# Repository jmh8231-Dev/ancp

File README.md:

# ANCP Rocket Motor Test Station (Rev 2.0)

> 고정추진제 로켓 모터(ANCP) 지상시험을 위한 **정밀 계측·점화 제어 스테이션**  
> 고정밀 아날로그 체인(로드셀/압력/열전대), **안전 중심 점화 시퀀스**, **2″ LCD(LVGL9 + SPI DMA)** GUI, PC 텔레메트리 지원

---

##  주요 기능

- **안전 중심 점화 플로우**
  - 물리 **IGN 스위치** 감지 → 카운트다운 → 온도/추력 인터록 → 핫와이어 제어
  - 모터/보드/PC 준비 상태 점검(미준비 시 시험 중지)
- **정밀 계측 체인**
  - 로드셀(추력), 챔버 압력, 노즐/내부 온도(열전대), IMU 진동
  - 메인/IGN 배터리 **셀 별 전압** + 메인 배터리 전류(INA219)
- **2″ LCD GUI (LVGL v9)**
  - **SPI DMA** 플러시(논블로킹), SquareLine Studio 기반 화면
  - Idle/Test/Config/Cal 페이지, FPS 확보 위해 라인 버퍼 + DMA 이중버퍼
- **EEPROM 기반 설정/보정**
  - **32B 페이지** 체크섬 저장 포맷(캘리브레이션 오프셋/설정값 무결성 보장)
- **PC/RF 텔레메트리**
  - 헤더·길이·페이로드·체크섬으로 구성된 패킷 전송
- **RTOS 태스킹**
  - sensing / gui / comms / control / logging 분리

---

##  하드웨어 개요

| 항목 | 부품 |
|---|---|
| MCU | **STM32H723VGT6** (H7, 12 MHz TCXO) |
| 정밀 ADC | **ADS1262IPW** (ΔΣ, 24-bit) |
| SPI 절연 | **ADuM4151** (MCU–ADC) |
| 기준전압 | **ADR4525D** |
| Op-Amp | **OPA189**, **MCP6022**, **TLV9351** |
| 전류 센서 | **INA219** (메인 배터리) |
| IMU | **BNO085** (I²C) |
| 온도 센서 | **AS6221** (MOSFET 온도) |
| EEPROM | **AT24C08C** (I²C) |
| 전원 | LM2596S-3.3, **CC6-1212DR-E**(±12 V) → **LT3045**(+5 V) / **LT3094**(−5 V) / **TPS79225**(+2.5 V) / **TPS72325**(−2.5 V) |
| 점화 경로 | **TC427** 게이트 드라이버 + **IRF1404** 파워 MOSFET, 물리 **IGN SW** |
| I/O | 2″ LCD, F1–F4 버튼, 부저, USB-UART(FT232RL), RF 모듈, ST-Link, 밸런스 잭 |

**3D 렌더 (Top)**  

**PCB 레이아웃(Top Routed)**  

---

##  펌웨어 개요

- **프레임워크**: STM32Cube HAL (+ FreeRTOS 선택)
- **GUI**: **LVGL v9** / **SquareLine Studio**(UI 설계)
- **LCD 드라이버**: **ST7789 (SPI4 + DMA)**  
  - `fw/Drivers/lcd/LCD_2inch_st7789_v9_dma.c` — ST7789 초기화 + DMA 라인 스트리머  
  - `fw/Drivers/lcd/LVGL9_ST7789_Port_ULP.c` — LVGL9 디스플레이 포트(플러시/세마포어)  
  - `fw/Drivers/board/DEV_Config_h7.c` — SPI4 DMA, D-Cache clean, TIM3 PWM 백라이트, OS-aware delay
- **정밀 ADC(ADS1262)**: SPI(절연) 드라이버, 채널/게인/SPS 매트릭스, 오프셋 CAL
- **EEPROM(AT24C08C)**: 페이지 쓰기/검증, 설정·보정값 저장
- **주요 태스크(권장)**: `task_gui`, `task_sense_fast`, `task_comms`, `task_control`, `task_logging`

### LVGL & LCD 초기화 예시
```c
// main.c
extern void lv_port_disp_init_st7789_v9_ulp(void);

void app_gui_init(void) {
    lv_init();
    lv_port_disp_init_st7789_v9_ulp();  // DMA flush, flush_wait 포함
    // SquareLine 생성 코드 호출 ...
}
```

> **D-Cache ON** 환경에서는 DMA 전 송신 버퍼에 대해 **SCB_CleanDCache_by_Addr()** 처리 필수. 위 파일들에 구현 포함.

---

##  캘리브레이션 & EEPROM 포맷

**ADC Zero-Offset CAL**: *(ch, gain, sps)* 조합별로 오프셋 저장. 부팅 시 전 페이지 스캔 → **이중 체크섬** 검증 → RAM LUT 로드.

```
[32B Page Format]  (1 페이지 = 4개의 Offset)
0-1   : "EP" (헤더)
2     : CH/Gain 상위 3비트(6..3)
3     : SPS
4-7   : OFFSET[ch][gain][sps] (int32/Q-format)
8-13  : 다음 CH/Gain/SPS + OFFSET
14-15 : CHECKSUM #1 (0..13)

16-17 : "EP"
18-19 : CH/Gain/SPS
20-25 : OFFSET
26-29 : 다음 CH/Gain/SPS + OFFSET
30-31 : CHECKSUM #2 (16..29)
```

- **쓰기 시퀀스**: 새 페이지 작성 → 읽기 검증 → 성공 시 구버전 페이지 폐기(저널링)
- **유효성 실패 시**: 기본 오프셋(0)로 부팅 + Cal 페이지 경고 표시

---

## 시험/점화 플로우

1. **Self-check**: 센서 연결/EEPROM 무결성/배터리 상태/PC 준비 여부
2. **IGN SW ON** → **ANCP Test** 모드 자동 진입
3. 로드셀 **Auto-tare** → **카운트다운**(가변)
4. 점화 로직(예시):
```c
if (mosfet_temp < T_th && thrust < F_th)  hotwire_on();
else if (mosfet_temp > T_th && thrust < F_th) { hotwire_off(); show_overheat(); }
else hotwire_off(); // ignition success
```
5. 실시간 데이터 **PC 전송** + 로깅

**전송 패킷(예시)**: `0x48 0x53 | type | len | payload | CRC16`

---

## 스키매틱 스냅샷

**Main Power**  

**MCU**  

**Analog/ADC/Isolation**  

---

## 빌드 & 플래시

- **툴체인**: STM32CubeIDE(H7), ARM GCC, (선택) FreeRTOS  
- **Cube 설정 핵심**  
  - SPI4 TX DMA(FIFO 사용), CS/DC/RST/BL GPIO  
  - TIM3 PWM → 백라이트  
  - 1 ms 타이머 → `lv_tick_inc()`  
  - D-Cache 사용 시 DMA 버퍼 **clean** 처리  
- **빌드**
  ```bash
  git clone https://github.com/jmh8231-Dev/ancp
  # STM32CubeIDE에서 .ioc 열기 → 빌드 → ST-Link로 플래시
  ```
- **첫 부팅**: Idle 화면 → 센서/배터리 상태 확인

---

## 문서 구조

```
ancp/
├─ fw/
│  ├─ Core/                 # CubeMX 생성 코드
│  ├─ Drivers/
│  │  ├─ lvgl/              # LVGL v9
│  │  ├─ lcd/               # LCD_2inch_st7789_v9_dma.c, LVGL9_ST7789_Port_ULP.c
│  │  └─ board/             # DEV_Config_h7.c 등
│  ├─ app/                  # tasks, ads1262, eeprom, telemetry, state machine
│  └─ middleware/           # FreeRTOS(선택)
├─ hw/                      # 회로/PCB/거버
├─ docs/
│  └─ images/               # 사진/스크린샷
└─ README.md
```

## 주의

- 방폭/방염 환경, 방호벽, 소화 장비, **E-Stop** 필수
- 시험 전 인터록/센서/전원/배선 재점검

---

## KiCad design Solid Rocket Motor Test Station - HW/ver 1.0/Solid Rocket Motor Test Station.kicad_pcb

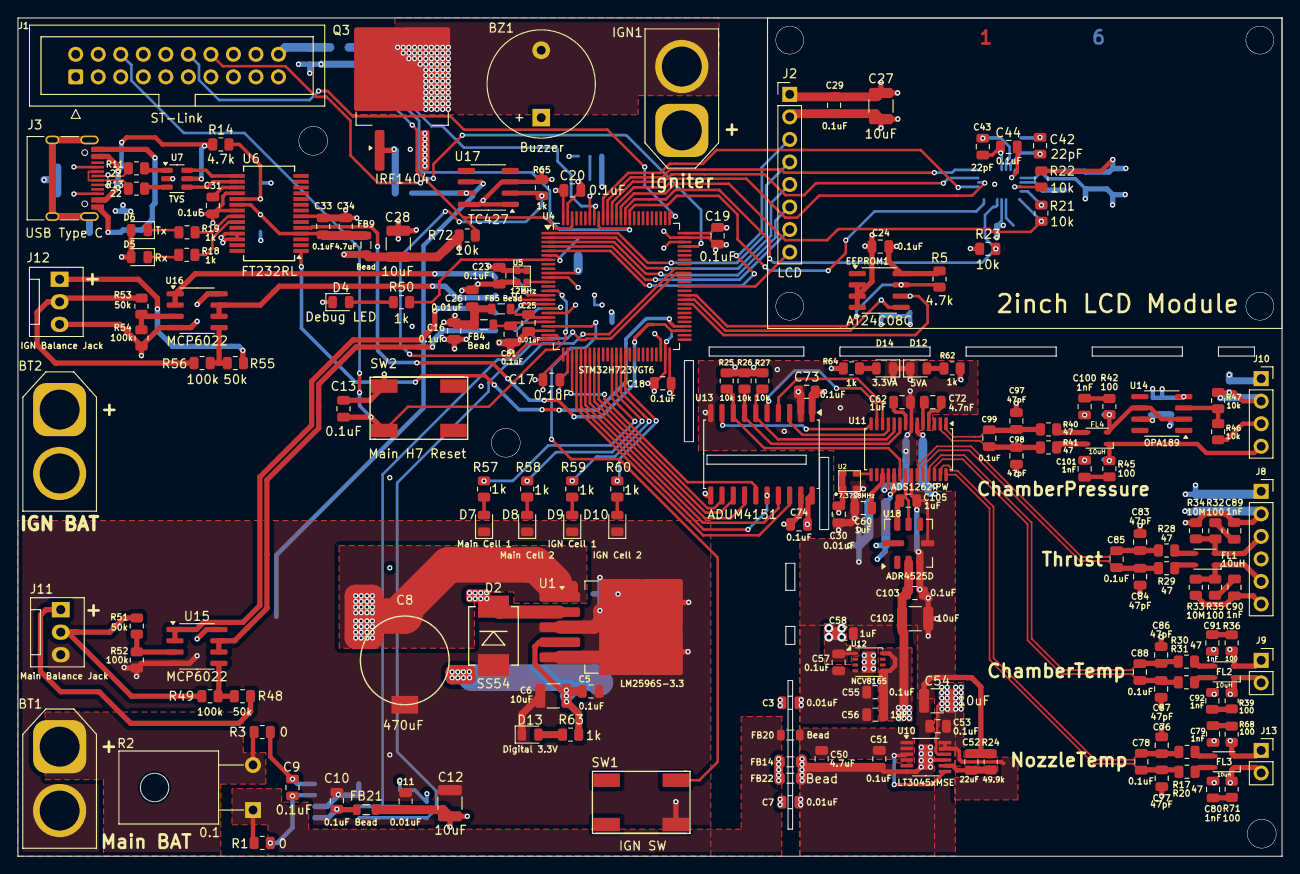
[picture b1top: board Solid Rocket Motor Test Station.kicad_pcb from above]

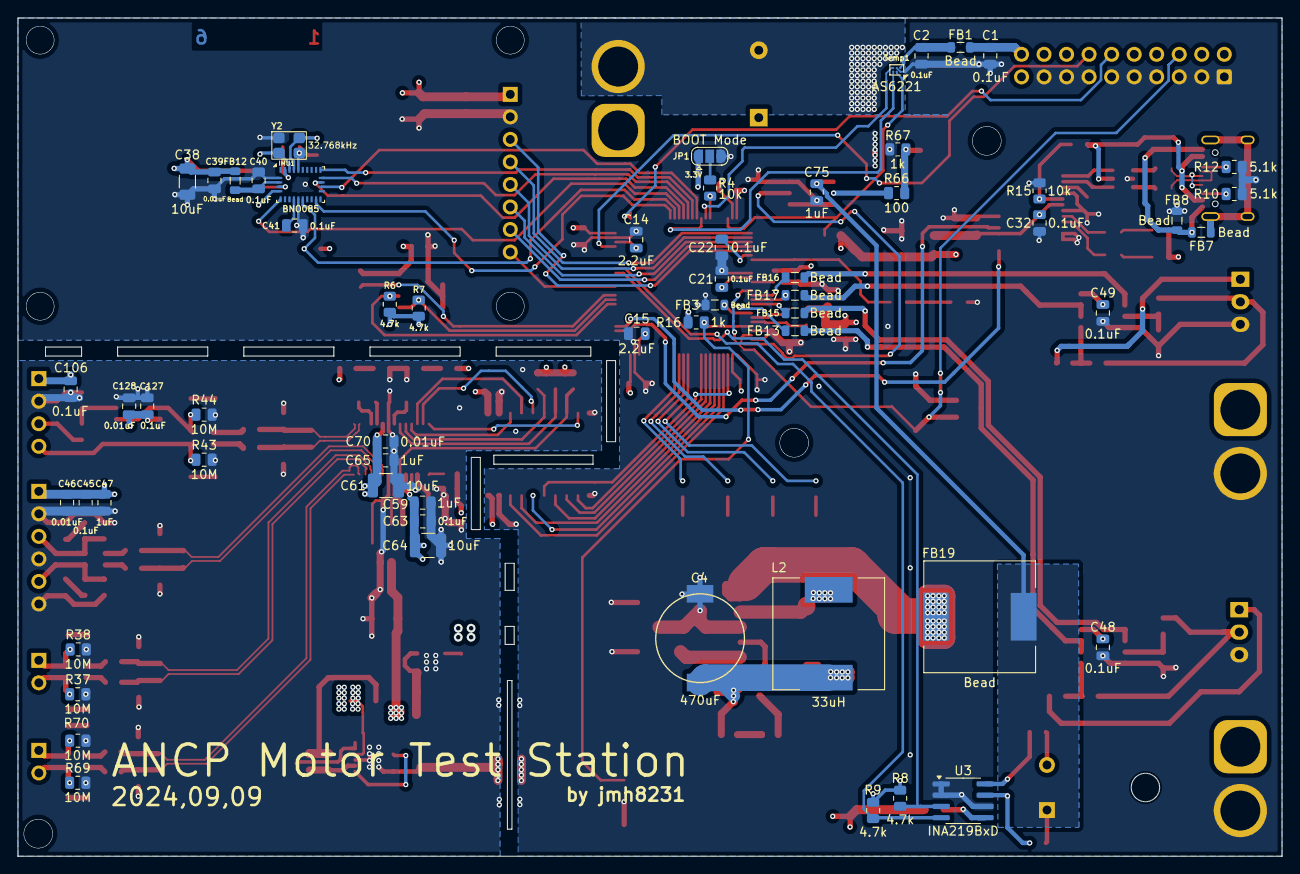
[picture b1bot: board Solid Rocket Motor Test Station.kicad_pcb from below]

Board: 6 copper layers, 142.5 x 94.5 mm, 235 parts (60 on the bottom side), 161 nets.

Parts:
BT1: Main BAT; AMASS_XT60-F_1x02_P7.20mm_Vertical
BT2: IGN BAT; AMASS_XT60-F_1x02_P7.20mm_Vertical
BZ1: Buzzer; Buzzer_12x9.5RM7.6
C1, C2, C5, C9, C10, C13, C16, C17, C18, C19, C20, C21, C22, C23, C24, C29, C31, C32, C33, C40, C41, C44, C45, C48, C49, C51, C53, C55, C57, C63, C73, C74, C78, C81, C85, C88, C99, C103, C106, C127: 0.1uF; C_0805_2012Metric
C3, C7, C11, C25, C26, C30, C39, C46, C70, C128: 0.01uF; C_0805_2012Metric
C4, C8: 470uF; MVG25WV470M
C6, C12, C27, C28, C54, C61, C64, C102: 10uF; C_1210_3225Metric
C14, C15: 2.2uF; C_0805_2012Metric
C34, C50: 4.7uF; C_0805_2012Metric
C38: 10uF; C_1206_3216Metric
C42, C43: 22pF; C_0805_2012Metric
C47, C56, C58, C59, C60, C62, C65, C75, C105: 1uF; C_0805_2012Metric
C52: 22uF; C_0805_2012Metric
C72: 4.7nF; C_0805_2012Metric
C76, C77, C83, C84, C86, C87, C97, C98: 47pF; C_0805_2012Metric
C79, C80, C89, C90, C91, C92, C100, C101: 1nF; C_0805_2012Metric
D2: SS54
D4: Debug LED; LED_0805_2012Metric
D5: Rx; LED_0805_2012Metric
D6: Tx; LED_0805_2012Metric
D7: Main Cell 1; LED_0805_2012Metric
D8: Main Cell 2; LED_0805_2012Metric
D9: IGN Cell 1; LED_0805_2012Metric
D10: IGN Cell 2; LED_0805_2012Metric
D12: 5VA; LED_0805_2012Metric
D13: Digital 3.3V; LED_0805_2012Metric
D14: 3.3VA; LED_0805_2012Metric
EEPROM1: AT24C08C; SOIC-8_3.9x4.9mm_P1.27mm
FB1, FB3, FB4, FB5, FB7, FB8, FB9, FB12, FB13, FB14, FB15, FB16, FB17, FB20, FB21, FB22: Bead; L_0805_2012Metric
FB19: Bead; L_12x12mm_H8mm
FL1, FL2, FL3, FL4: 10uH; L_CommonModeChoke_TDK_ACM2520-2P
IGN1: Igniter; AMASS_XT60-M_1x02_P7.20mm_Vertical
IMU1: BNO085; LGA-28_5.2x3.8mm_P0.5mm
J1: ST-Link; IDC-Header_2x10_P2.54mm_Vertical
J2: LCD; PinHeader_1x08_P2.54mm_Vertical
J3: USB Type C; USB_C_Receptacle_HRO_TYPE-C-31-M-12
J8: Thrust; PinSocket_1x06_P2.54mm_Vertical
J9: ChamberTemp; PinSocket_1x02_P2.54mm_Vertical
J10: ChamberPressure; PinSocket_1x04_P2.54mm_Vertical
J11: Main Balance Jack; FanPinHeader_1x03_P2.54mm_Vertical
J12: IGN Balance Jack; FanPinHeader_1x03_P2.54mm_Vertical
J13: NozzleTemp; PinSocket_1x02_P2.54mm_Vertical
JP1: BOOT Mode; SolderJumper-3_P1.3mm_Open_RoundedPad1.0x1.5mm
L2: 33uH; L_12x12mm_H8mm
Q3: IRF1404; TO-263-2
R1, R3: 0; R_0805_2012Metric
R2: 0.1; TO-126-2_Horizontal_TabDown
R4, R15, R21, R22, R23, R25, R26, R27, R46, R47, R72: 10k; R_0805_2012Metric
R5, R6, R7, R8, R9, R14: 4.7k; R_0805_2012Metric
R10, R12: 5.1k; R_0805_2012Metric
R11, R13: 22; R_0805_2012Metric
R16, R18, R19, R50, R57, R58, R59, R60, R62, R63, R64, R65, R67: 1k; R_0805_2012Metric
R17, R20, R28, R29, R30, R31, R40, R41: 47; R_0805_2012Metric
R24: 49.9k; R_0805_2012Metric
R32, R35, R36, R39, R42, R45, R66, R68, R71: 100; R_0805_2012Metric
R33, R34, R37, R38, R43, R44, R69, R70: 10M; R_0805_2012Metric
R48, R51, R53, R55: 50k; R_0805_2012Metric
R49, R52, R54, R56: 100k; R_0805_2012Metric
SW1: IGN SW; SW_SMD_IT-1107
SW2: Main H7 Reset; SW_SMD_IT-1107
Temp1: AS6221; WLCSP-6_1.4x1.0mm_P0.4mm
U1: LM2596S-3.3; TO-263-5_TabPin3
U2: 7.3728MHz; ASDMB-OSC
U3: INA219BxD; SOIC-8_3.9x4.9mm_P1.27mm
U4: STM32H723VGT6; LQFP-100_14x14mm_P0.5mm
U5: 12MHz; ECS-TXO-2016
U6: FT232RL; SSOP-28_5.3x10.2mm_P0.65mm
U7: TVS; SOT-23-6
U10: LT3045xMSE; MSOP-12-1EP_3x4mm_P0.65mm_EP1.65x2.85mm
U11: ADS1262IPW; TSSOP-28_4.4x9.7mm_P0.65mm
U12: NCV8165; DFN-8-1EP_3x3mm_P0.65mm_EP1.55x2.4mm
U13: ADUM4151; SOIC-20W_7.5x12.8mm_P1.27mm
U14: OPA189; SOIC-8_3.9x4.9mm_P1.27mm
U15, U16: MCP6022; SOIC-8_3.9x4.9mm_P1.27mm
U17: TC427; SOIC-8_3.9x4.9mm_P1.27mm
U18: ADR4525D; Analog_LCC-8_5x5mm_P1.27mm
Y2: 32.768kHz; XC32M4

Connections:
+3.3V: BZ1.1 (-), C1.2, C4.1, C5.1, C6.1, C11.1, C12.1, C16.1, C17.1, C18.1, C19.1, C20.1, C21.1, C22.1, C23.1, C24.1, C26.2, C27.1, C28.1, C29.1, C38.1, C39.2, C44.1, C48.2, C49.2, C74.2, D5.2 (A), D6.2 (A), EEPROM1.8 (VCC), FB1.1, FB4.2, FB5.1, FB9.2, FB12.1, FB21.2, IMU1.5 (PS1), IMU1.28 (VDDIO), J1.19, J1.20, J2.1, JP1.1 (A), L2.2, R5.1, R6.1, R7.1, R8.1, R9.1, R16.1, R21.2, R22.2, R23.2, R63.1, R72.1, U1.4 (FB), U4.6 (VBAT), U4.11 (VDD), U4.27 (VDD), U4.50 (VDD), U4.75 (VDD), U4.100 (VDD), U5.1 (EN), U5.4 (Vcc), U13.20 (VDD2), U15.8 (V+), U16.8 (V+)
+3.3VA: C30.1, C57.2, C58.1, C59.1, C63.1, C64.1, C73.2, R25.1, R26.1, R27.1, R64.1, U2.1 (EN), U2.4 (Vcc), U11.19 (DVDD), U12.1 (OUT), U13.1 (VDD1)
+5VA: C45.1, C46.1, C47.1, C53.2, C54.1, C55.2, C56.1, C61.1, C65.1, C70.1, C102.1, C103.1, C106.1, C127.2, C128.2, J8.1, J10.1, R62.1, U10.10 (OUTS), U10.11 (OUT), U10.12 (OUT), U11.6 (AVDD), U12.5 (EN), U12.8 (IN), U14.7 (V+), U18.2 (VIN)
+8V: C75.2, FB19.1, FB20.1, R1.2, R2.1, U17.6 (VDD)
+BATT: BT2.1 (+), IGN1.1
-BATT: BZ1.2 (+), IGN1.2, Q3.2 (D)
ADC_CS: U4.28 (PA4), U13.15 (SCS)
ADC_DRDY: U4.34 (PB0), U13.12 (VIC)
ADC_MISO: U4.30 (PA6), U13.16 (SO)
ADC_MOSI: U4.31 (PA7), U13.17 (SI)
ADC_RESET: U4.33 (PC5), U13.13 (VOB)
ADC_SCLK: U4.29 (PA5), U13.18 (SCLK)
ADC_START: U4.32 (PC4), U13.14 (VOA)
AS6221_SCL: Temp1.A3 (SCL), U4.92 (PB6)
AS6221_SDA: Temp1.B3 (SDA), U4.93 (PB7)
BAT1(3.7V): J11.2, R49.2, R51.1
BAT2(7.4V): J11.1, R48.1
BAT_SCL: R9.2, U3.4 (SCL), U4.67 (PA8)
BAT_SDA: R8.2, U3.3 (SDA), U4.66 (PC9)
BNO085_CS: IMU1.18 (H_CSN), U4.88 (PD7)
BNO085_INT: IMU1.14 (H_INTN), U4.85 (PD4)
BNO085_MISO: IMU1.20 (H_SDA/MISO/TX), U4.90 (PB4(NJTRST))
BNO085_MOSI: IMU1.17 (H_SA0/MOSI), U4.91 (PB5)
BNO085_PS0: IMU1.6 (PS0/WAKE), R21.1, U4.87 (PD6)
BNO085_RST: IMU1.11 (NRST), R23.1, U4.86 (PD5)
BNO085_SCK: IMU1.19 (H_SCL/SCK/RX), U4.89 (PB3(JTDO)
BOOT0: R4.2, U4.94 (BOOT0)
Ch1_N: C84.2, C85.2, R29.1, U11.24 (AIN3)
Ch1_P: C83.1, C85.1, R28.1, U11.23 (AIN2)
Ch2_N: C87.2, C88.2, R31.1, U11.26 (AIN5)
Ch2_P: C86.1, C88.1, R30.1, U11.25 (AIN4)
Ch3_N: C77.2, C78.2, R20.1, U11.28 (AIN7)
Ch3_P: C76.1, C78.1, R17.1, U11.27 (AIN6)
Ch4_N: C98.2, C99.2, R41.1, U11.2 (AIN9)
Ch4_P: C97.1, C99.1, R40.1, U11.1 (AIN8)
D+: U6.15 (USBD+), U7.6
D-: U6.16 (USBD-), U7.4
Debug_LED: R50.1, U4.7 (PC13)
EEPROM_SCL: EEPROM1.6 (SCL), R6.2, U4.59 (PD12)
EEPROM_SDA: EEPROM1.5 (SDA), R7.2, U4.60 (PD13)
EEPROM_WP: EEPROM1.7 (WP), R5.2, U4.61 (PD14)
FET_TEMP_INT: R72.2, Temp1.A2 (Alert/ADD1), U4.98 (PE1)
GND: BT1.2 (-), BT2.2 (-), C1.1, C2.2, C3.2, C4.2, C5.2, C6.2, C7.2, C8.2, C10.2, C11.2, C12.2, C13.1, C14.1, C15.1, C16.2, C17.2, C18.2, C19.2, C20.2, C21.2, C22.2, C23.2, C24.2, C25.1, C26.1, C27.2, C28.2, C29.2, C31.2, C32.2, C33.2, C34.2, C38.2, C39.1, C40.2, C41.1, C42.2, C43.2, C44.2, C48.1, C49.1, C74.1, C75.1, C81.2, D2.2 (A), D4.1 (K), D7.1 (K), D8.1 (K), D9.1 (K), D10.1 (K), D13.1 (K), EEPROM1.2 (A1), EEPROM1.3 (A2), EEPROM1.4 (GND), FB3.2, FB8.2, FB14.1, FB22.1, IMU1.2 (GND), IMU1.10 (CLKSEL0), IMU1.25 (GND), J1.1, J1.3, J1.5, J1.7, J1.9, J1.11, J1.13, J1.15, J1.17, J2.2, J11.3, J12.3, JP1.3 (B), Q3.3 (S), R10.2, R12.2, R15.2, R52.2, R54.2, R65.1, R67.2, SW1.3, SW2.3, Temp1.A1 (VSS), Temp1.B2 (ADD0), U1.3 (GND), U1.5 (~ON/OFF), U3.1 (A1), U3.2 (A0), U3.6 (GND), U4.10 (VSS), U4.23 (PA1), U4.25 (PA3), U4.26 (VSS), U4.49 (VSS), U4.74 (VSS), U4.99 (VSS), U5.2 (GND), U6.7 (GND), U6.18 (GND), U6.21 (GND), U6.25 (AGND), U6.26 (TEST), U7.2, U13.11 (GND2), U13.19 (GND2), U15.4 (V-), U16.4 (V-), U17.1 (NC), U17.3 (GND), U17.8 (NC), Y2.2, Y2.4
IGN_BAT1(3.7V): J12.2, R53.1, R56.2
IGN_BAT2(7.4V): J12.1, R55.1
IGN_Cell1_ADC: FB16.2, U4.15 (PC0)
IGN_Cell2_ADC: FB17.2, U4.16 (PC1)
IGN_SW: R16.2, SW1.1, U4.22 (PA0)
IGN_Signal: R65.2, U4.24 (PA2), U17.2 (IN_A)
I_Power_Cell1: R59.1, U4.39 (PE9)
I_Power_Cell2: R60.1, U4.40 (PE10)
LCD_BL: J2.8, U4.63 (PC6)
LCD_CS: J2.5, U4.2 (PE3)
LCD_DC: J2.6, U4.3 (PE4)
LCD_MOSI: J2.3, U4.5 (PE6)
LCD_RST: J2.7, U4.4 (PE5)
LCD_SCLK: J2.4, U4.1 (PE2)
LoadCell_N: FL1.4, R29.2
LoadCell_P: FL1.3, R28.2
M_Power_Cell1: R57.1, U4.37 (PE7)
M_Power_Cell2: R58.1, U4.38 (PE8)
MainMCU_12MHz: U4.12 (PH0), U5.3 (OUT)
Main_Cell1_ADC: FB15.2, U4.17 (PC2_C)
Main_Cell2_ADC: FB13.2, U4.18 (PC3_C)
Main_Rx: U4.54 (PB15), U6.1 (TXD)
Main_Tx: U4.53 (PB14), U6.5 (RXD)
unnamed: BT1.1 (+), R2.2, R3.1
unnamed: C14.2, U4.73 (VCAP)
unnamed: C15.2, U4.48 (VCAP)
unnamed: C79.2, R68.1
unnamed: C80.2, R71.1
unnamed: C89.2, R32.1
unnamed: C90.2, R35.1
unnamed: C91.2, R36.1
unnamed: C92.2, R39.1
unnamed: C100.2, R42.1
unnamed: C101.2, R45.1
unnamed: D2.1 (K), L2.1, U1.2 (OUT)
unnamed: D4.2 (A), R50.2
unnamed: D5.1 (K), R18.2
unnamed: D6.1 (K), R19.2
unnamed: D7.2 (A), R57.2
unnamed: D8.2 (A), R58.2
unnamed: D9.2 (A), R59.2
unnamed: D10.2 (A), R60.2
unnamed: D12.2 (A), R62.2
unnamed: D13.2 (A), R63.2
unnamed: D14.2 (A), R64.2
unnamed: FB7.2, FB8.1, J3.A1 (GND), J3.A12 (GND), J3.B1 (GND), J3.B12 (GND)
unnamed: IMU1.4 (BOOTN), R22.1
unnamed: C41.2, IMU1.9 (CAP)
unnamed: C40.1, FB12.2, IMU1.3 (VDD)
unnamed: C42.1, IMU1.27 (XIN32), Y2.3
unnamed: C43.1, IMU1.26 (XOUT32/CLKSEL1), Y2.1
unnamed: J3.A5 (CC1), R12.1
unnamed: J3.B5 (CC2), R10.1
unnamed: FB7.1, J3.S1 (SHIELD)
unnamed: J10.3, R46.2
unnamed: JP1.2 (C), R4.1
unnamed: Q3.1 (G), R66.2, R67.1
unnamed: R11.2, U7.1
unnamed: R13.2, U7.3
unnamed: C2.1, FB1.2, Temp1.B1 (VDD)
unnamed: C8.1, FB19.2, U1.1 (VIN)
unnamed: C9.2, R3.2, U3.8 (IN+)
unnamed: C9.1, R1.1, U3.7 (IN-)
unnamed: C10.1, FB21.1, U3.5 (VS)
unnamed: C81.1, FB4.1, U4.21 (VDDA)
unnamed: C25.2, FB5.2, U4.20 (VREF+)
unnamed: FB3.1, U4.19 (VSSA)
unnamed: C31.1, U6.17 (3V3OUT)
unnamed: R18.1, U6.23 (CBUS0)
unnamed: R19.1, U6.22 (CBUS1)
unnamed: C32.1, C33.1, C34.1, FB9.1, U6.4 (VCCIO), U6.20 (VCC)
unnamed: R14.2, R15.1, U6.19 (~RESET)
unnamed: C50.1, C51.1, FB20.2, U10.1 (IN), U10.2 (IN), U10.3 (IN), U10.4 (EN/UV), U10.7 (PGFB)
unnamed: C52.1, R24.2, U10.8 (SET)
unnamed: C60.2, U11.17 (BYPASS)
unnamed: C72.2, U11.5 (CAPN)
unnamed: C72.1, U11.4 (CAPP)
unnamed: C62.2, U11.8 (REFOUT)
unnamed: U2.3 (OUT), U11.15 (XTAL1/CLKIN)
unnamed: R46.1, R47.2, U14.3 (+)
unnamed: R51.2, R52.1, U15.3 (+)
unnamed: FB15.1, U15.1, U15.2 (-)
unnamed: R48.2, R49.1, U15.5 (+)
unnamed: FB13.1, U15.6 (-), U15.7
unnamed: R53.2, R54.1, U16.3 (+)
unnamed: FB16.1, U16.1, U16.2 (-)
unnamed: R55.2, R56.1, U16.5 (+)
unnamed: FB17.1, U16.6 (-), U16.7
unnamed: R66.1, U17.7 (OUT_A)
PressureSensor_N: FL4.4, R41.2
PressureSensor_P: FL4.3, R40.2
Ref_N: C3.1, C7.1, C30.2, C45.2, C46.2, C47.2, C50.2, C51.2, C52.2, C53.1, C54.2, C55.1, C56.2, C57.1, C58.2, C59.2, C60.1, C61.2, C62.1, C63.2, C64.2, C65.2, C70.2, C73.1, C76.2, C77.1, C79.1, C80.1, C83.2, C84.1, C86.2, C87.1, C89.1, C90.1, C91.1, C92.1, C97.2, C98.1, C100.1, C101.1, C102.2, C103.2, C105.1, C106.2, C127.1, C128.1, D12.1 (K), D14.1 (K), FB14.2, FB22.2, J8.2, J8.4, J8.6, J10.2, R24.1, R33.2, R34.2, R37.2, R38.2, R43.2, R44.2, R47.1, R69.2, R70.2, U2.2 (GND), U10.6 (ILIM), U10.9 (GND), U10.13 (GND), U11.7 (AVSS), U11.18 (DGND), U11.22 (AIN1), U12.4 (GND), U12.9 (EXP), U13.2 (GND1), U13.10 (GND1), U14.4 (V-), U18.3 (GND_FORCE), U18.4 (GND_SENSE)
Ref_P: C105.2, U11.21 (AINO), U18.6 (VOUT_SENSE), U18.7 (VOUT_FORCE)
ST-Link_Reset: C13.2, J1.6, SW2.1, U4.14 (NRST)
ST-Link_SWCLK: J1.12, U4.76 (PA14(JTCK)
ST-Link_SWDIO: J1.14, U4.72 (PA13(JTMS)
Thermocouple_N: FL2.4, R31.2
Thermocouple_N1: FL3.4, R20.2
Thermocouple_P: FL2.3, R30.2
Thermocouple_P1: FL3.3, R17.2
USBVcc: J3.A4 (VBUS), J3.A9 (VBUS), J3.B4 (VBUS), J3.B9 (VBUS), R14.1, U7.5
adc_CS: R27.2, U11.10 (CS), U13.6 (MCS)
adc_DRDY: U11.14 (DRDY), U13.9 (VOC)
adc_MISO: U11.13 (MISO/DRDY), U13.5 (MI)
adc_MOSI: U11.12 (MOSI), U13.4 (MO)
adc_RESET: R25.2, U11.20 (RESET/PWDN), U13.8 (VIB)
adc_SCLK: U11.11 (SCLK), U13.3 (MCLK)
adc_START: R26.2, U11.9 (START), U13.7 (VIA)
d+: J3.A6 (D+), J3.B6 (D+), R11.1
d-: J3.A7 (D-), J3.B7 (D-), R13.1
loadCell_N: FL1.1, J8.5, R33.1, R35.2
loadCell_P: FL1.2, J8.3, R32.2, R34.1
pressureSensor_N: FL4.1, J10.4, R43.1, R45.2
pressureSensor_P: FL4.2, R42.2, R44.1, U14.2 (-), U14.6
thermocouple_N: FL2.1, J9.2, R37.1, R39.2
thermocouple_N1: FL3.1, J13.2, R69.1, R71.2
thermocouple_P: FL2.2, J9.1, R36.2, R38.1
thermocouple_P1: FL3.2, J13.1, R68.2, R70.1

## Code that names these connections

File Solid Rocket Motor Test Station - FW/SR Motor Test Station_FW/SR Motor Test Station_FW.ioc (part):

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Mcu.Name=STM32H723VGTx
Mcu.Package=LQFP100
Mcu.UserName=STM32H723VGTx
PA0.GPIOParameters=GPIO_Label
PA0.GPIO_Label=IGN_Button
PA0.Signal=GPXTI0
PA1.GPIOParameters=GPIO_Label
PA1.GPIO_Label=IGN_Cell1_ADC
PA1.Mode=IN17-Single-Ended
PA1.Signal=ADC1_INP17
PA10.GPIOParameters=GPIO_Label
PA10.GPIO_Label=RF_M1
PA10.Signal=GPIO_Output
PA11.GPIOParameters=GPIO_Label
PA11.GPIO_Label=RF_Tx
PA11.Mode=Asynchronous
PA11.Signal=UART4_RX
PA12.GPIOParameters=GPIO_Label
PA12.GPIO_Label=RF_Rx
PA12.Mode=Asynchronous
PA12.Signal=UART4_TX
PA13(JTMS/SWDIO).Mode=Serial_Wire
PA13(JTMS/SWDIO).Signal=DEBUG_JTMS-SWDIO
PA14(JTCK/SWCLK).Mode=Serial_Wire
PA14(JTCK/SWCLK).Signal=DEBUG_JTCK-SWCLK
PA2.GPIOParameters=GPIO_Label
PA2.GPIO_Label=IGN_Signal
PA2.Signal=GPIO_Output
PA3.GPIOParameters=GPIO_Label
PA3.GPIO_Label=IGN_Cell2_ADC
PA3.Signal=ADCx_INP15
PA4.GPIOParameters=GPIO_Label
PA4.GPIO_Label=ADS1262_CS
PA4.Signal=GPIO_Output
PA5.GPIOParameters=GPIO_Label
PA5.GPIO_Label=ADS1262_SCK
PA5.Mode=Full_Duplex_Master
PA5.Signal=SPI1_SCK
PA6.GPIOParameters=GPIO_Label
PA6.GPIO_Label=ADS1262_MISO
PA6.Mode=Full_Duplex_Master
PA6.Signal=SPI1_MISO
PA7.GPIOParameters=GPIO_Label
PA7.GPIO_Label=ADS1262_MOSI
PA7.Mode=Full_Duplex_Master
PA7.Signal=SPI1_MOSI
PA8.GPIOParameters=GPIO_Label
PA8.GPIO_Label=INA219_SCL
PA8.Mode=I2C
PA8.Signal=I2C3_SCL
PA9.GPIOParameters=GPIO_Label
PA9.GPIO_Label=RF_M0
PA9.Signal=GPIO_Output
PB0.GPIOParameters=GPIO_Label
PB0.GPIO_Label=ADS1262_DRDY
PB0.Signal=GPIO_Input
PB14.GPIOParameters=GPIO_Label
PB14.GPIO_Label=Debug_Tx
PB14.Mode=Asynchronous
PB14.Signal=USART1_TX
PB15.GPIOParameters=GPIO_Label
PB15.GPIO_Label=Debug_Rx
PB15.Mode=Asynchronous
PB15.Signal=USART1_RX
PB3(JTDO/TRACESWO).GPIOParameters=GPIO_Label
PB3(JTDO/TRACESWO).GPIO_Label=BNO085_SCK
PB3(JTDO/TRACESWO).Mode=Full_Duplex_Master
PB3(JTDO/TRACESWO).Signal=SPI3_SCK
PB4(NJTRST).GPIOParameters=GPIO_Label
PB4(NJTRST).GPIO_Label=BNO085_MISO
PB4(NJTRST).Mode=Full_Duplex_Master
PB4(NJTRST).Signal=SPI3_MISO
PB5.GPIOParameters=GPIO_Label
PB5.GPIO_Label=BNO085_MOSI
PB5.Mode=Full_Duplex_Master
PB5.Signal=SPI3_MOSI
PB6.GPIOParameters=GPIO_Label
PB6.GPIO_Label=AS6221_SCL
PB6.Mode=I2C
PB6.Signal=I2C1_SCL
PB7.GPIOParameters=GPIO_Label
PB7.GPIO_Label=AS6221_SDA
PB7.Mode=I2C
PB7.Signal=I2C1_SDA
PC1.GPIOParameters=GPIO_Label
PC1.GPIO_Label=Main_Cell1_ADC
PC1.Signal=ADCx_INP11
PC13.GPIOParameters=GPIO_Label
PC13.GPIO_Label=LD1
PC13.Signal=GPIO_Output
PC2_C.GPIOParameters=GPIO_Label
PC2_C.GPIO_Label=Main_Cell2_ADC
PC2_C.Mode=IN0-Single-Ended
PC2_C.Signal=ADC3_INP0
PC3_C.GPIOParameters=GPIO_Label
PC3_C.GPIO_Label=Main_Cell3_ADC
PC3_C.Mode=IN1-Single-Ended
PC3_C.Signal=ADC3_INP1
PC4.GPIOParameters=GPIO_Label
PC4.GPIO_Label=ADS1262_START
PC4.Signal=GPIO_Output
PC5.GPIOParameters=GPIO_Label
PC5.GPIO_Label=ADS1262_RST
PC5.Signal=GPIO_Output
PC6.GPIOParameters=GPIO_Speed,GPIO_Label
PC6.GPIO_Label=LCD_BL
PC6.GPIO_Speed=GPIO_SPEED_FREQ_VERY_HIGH
PC6.Signal=S_TIM3_CH1
PC7.GPIOParameters=GPIO_Label
PC7.GPIO_Label=Buzzer
PC7.Signal=S_TIM3_CH2
PC9.GPIOParameters=GPIO_Label
PC9.GPIO_Label=INA219_SDA
PC9.Mode=I2C
PC9.Signal=I2C3_SDA
PD0.GPIOParameters=GPIO_Label
PD0.GPIO_Label=F4_Button
PD0.Signal=GPIO_Input
PD1.GPIOParameters=GPIO_Label
PD1.GPIO_Label=F3_Button
PD1.Signal=GPIO_Input
PD12.GPIOParameters=GPIO_Label
PD12.GPIO_Label=EEPROM_SCL
PD12.Mode=I2C
PD12.Signal=I2C4_SCL
PD13.GPIOParameters=GPIO_Label
PD13.GPIO_Label=EEPROM_SDA
PD13.Mode=I2C
PD13.Signal=I2C4_SDA
PD14.GPIOParameters=GPIO_Label
PD14.GPIO_Label=EEPROM_WP
PD14.Signal=GPIO_Output
PD2.GPIOParameters=GPIO_Label
PD2.GPIO_Label=F2_Button
PD2.Signal=GPIO_Input
PD3.GPIOParameters=GPIO_Label
PD3.GPIO_Label=F1_Button
PD3.Signal=GPIO_Input
PD4.GPIOParameters=GPIO_Label
PD4.GPIO_Label=BNO085_INT
PD4.Signal=GPIO_Input
PD5.GPIOParameters=GPIO_Label
PD5.GPIO_Label=BNO085_RST
PD5.Signal=GPIO_Output
PD6.GPIOParameters=GPIO_Label
PD6.GPIO_Label=BNO085_PS0
PD6.Signal=GPXTI6
PD7.GPIOParameters=GPIO_Label
PD7.GPIO_Label=BNO085_CS
PD7.Signal=GPIO_Output
PE2.GPIOParameters=GPIO_Speed,GPIO_PuPd,GPIO_Label
PE2.GPIO_Label=LCD_SCK
PE2.GPIO_PuPd=GPIO_PULLDOWN
PE2.GPIO_Speed=GPIO_SPEED_FREQ_VERY_HIGH
PE2.Mode=TX_Only_Simplex_Unidirect_Master
PE2.Signal=SPI4_SCK
PE3.GPIOParameters=GPIO_Speed,PinState,GPIO_Label
PE3.GPIO_Label=LCD_CS
PE3.GPIO_Speed=GPIO_SPEED_FREQ_VERY_HIGH
PE3.PinState=GPIO_PIN_SET
PE3.Signal=GPIO_Output
PE4.GPIOParameters=GPIO_Speed,PinState,GPIO_Label
PE4.GPIO_Label=LCD_DC
PE4.GPIO_Speed=GPIO_SPEED_FREQ_VERY_HIGH
PE4.PinState=GPIO_PIN_SET
PE4.Signal=GPIO_Output
PE5.GPIOParameters=GPIO_Speed,PinState,GPIO_Label
PE5.GPIO_Label=LCD_RST
PE5.GPIO_Speed=GPIO_SPEED_FREQ_VERY_HIGH
PE5.PinState=GPIO_PIN_SET
PE5.Signal=GPIO_Output
PE6.GPIOParameters=GPIO_Speed,GPIO_Label
PE6.GPIO_Label=LCD_MOSI
PE6.GPIO_Speed=GPIO_SPEED_FREQ_VERY_HIGH
PE6.Mode=TX_Only_Simplex_Unidirect_Master
PE6.Signal=SPI4_MOSI
PH0-OSC_IN.Mode=HSE-External-Oscillator
PH0-OSC_IN.Signal=RCC_OSC_IN
PH1-OSC_OUT.Mode=HSE-External-Oscillator
PH1-OSC_OUT.Signal=RCC_OSC_OUT
RCC.HSE_VALUE=12000000
RCC.SYSCLKFreq_VALUE=550000000
RCC.SYSCLKSource=RCC_SYSCLKSOURCE_PLLCLK
board=custom

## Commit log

2025-08-25 ancp test staton hw v1.0
2025-08-25 hw v2.0 update
2025-08-25 ancp motor test station fw v1.0 update
2025-08-25 img update
